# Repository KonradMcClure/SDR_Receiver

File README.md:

# Low-Cost Software Defined Radio Receiver
The goal of this project was to design a low-cost software-defined radio (SDR) receiver. This project was done for my Walla Walla University Electronics II course with my partner [Caleb Froelich](https://github.com/froeca).

## Design Objectives
Our professor, [Dr. Rob Frohne](https://github.com/frohro), gave us the following design objectives:
  1. Minimum discernible signal less than 1 uV
  2. Good image rejection
  3. Low noise figure
  4. Inexpensive to build ($25 component budget)
  
My partner, Caleb, and I set our own design objectives as well to help narrow down the design we settled on:
  1. **Simple Design**: We wanted our design to be easy to understand and construct. As such we avoided using transformers and used a Tayloe Mixer which has a relatively easy to understand design.
  2. **Ease of Construction**: Since this class took place during an online quarter due to COVID-19, we wanted to make sure construction wouldn't be too difficult without the usual tools we have in our lab. This decision shaped our board layout and part selection (picking through-hole parts as opposed to surface-mount when possible).
  3. **Ease and Quality of Amplification**: Most of the cost that goes into the board went into getting good, low-noise operational amplifiers. The instrumentation amps we chose use a single resistor to set the gain, making it easy to switch out and test different gain values.

## Overview
The Software Defined Radio (SDR) receiver connects to an antenna and covers the filtering, mixing, and amplification of the desired signal. It then connects a sound card within a computer and software handles the demodulation of the signal into playable audio. The mixing is handled using an Arduino Nano running code provided to us by our Professor, [Dr. Rob Frohne](https://github.com/frohro), which interfaces with [Quisk](https://james.ahlstrom.name/quisk/), an SDR that controls the receiver through the Arduino. Using Quisk, the radio can be tuned to a certain frequency by adjusting the speed of the local oscillator used in the mixing process. Our budget on this project to keep with the low-cost aspect was about $30 including fabrication of the PCB and the required components. 

# Theory

The basics of the SDR Receiver are shown above in the block diagram, with the blue components being defined by software. An antenna picks up the radio signal and passes it through a bandpass filter. This filter will attenuate any signals outside our desired range of 5 – 10 MHz. This is then passed through a Tayloe Mixer, also known as the Tayloe Quadrature Product Detector. The Tayloe Mixer is a simple and efficient mixer that uses a 1:4 demultiplexer and operational amplifiers to generate the I and Q quadrature signals for demodulation. After the signal has been split into four bandbase signals, they are amplified and combined into the I and Q quadrature signals. Those signals go through a final Low-Pass filter that will attenuate signals above 100KHz in frequency, effectively smoothing the output signal. This signal is then sent via 3.5mm audio cable to the soundcard which demodulates the signal. Quisk can then read the input from the sound card and play it. Quisk also interfaces to the Arduino Nano to set the speed of the local oscillator for tuning into the desired frequency.

# Rev 2 Design

Here is the full design schematic, which we'll break down piece by piece below. You can look at the full image [here](https://github.com/KonradMcClure/SDR_Receiver/blob/master/images/Schematics/Rev2_Schem.svg) or download the [KiCad](https://kicad-pcb.org/) project [here](https://github.com/KonradMcClure/SDR_Receiver/tree/master/SDRReciever) to take a closer look yourself.

This page is also acting as a report of the design we had for our class project. If the design is continued on in the future, I will likely move this description to the Wiki and update it with the new one.

## Bandpass Filter

The bandpass filter is a 3rd-Order, Series-First, Bessel filter that was generated using the RF Tools LC Filters Design Tool. It is designed to have input and output impedances of 50 Ω. The motivation to use a series-first configuration came from the capacitor C2 acting as a blockade for any DC signal coming in through the antenna. This would allow us better control over the DC voltage offset that is later required for our single-supply op-amps. 

## DC Voltage Offset

Since we didn't want to create a negative supply for our op-amps, we opted for using them with a single supply and giving our signal a DC offset that sits in the middle between the 4.3V supply and ground. This offset was done via a simple voltage divider of two 10k resistors from 4.3V to GND.

## Tayloe Mixer 

The Tayloe Mixer is a mixer design as seen in [this paper](http://www.norcalqrp.org/files/Tayloe_mixer_x3a.pdf) by Dan Tayloe. We chose it due to its relatively simple and elegant design. It utilizes a [two-channel SN74CBT multiplexer](http://www.ti.com/lit/ds/symlink/sn74cbt3253.pdf?ts=1591655665924) and a pair of [INA821ID single gain resistor instrumentation amplifiers](http://www.ti.com/lit/ds/symlink/ina821.pdf?HQS=TI-null-null-mousermode-df-pf-null-wwe&DCM=yes&ref_url=https%3A%2F%2Fwww.mouser.com%2F&distId=26). To be more specific, Tayloe describes this as a "switching integrator," rather than a mixer, since a mixer normally produces both a sum and difference frequency of the RF and LO signals, while this design only produces the difference frequency. Acknowledging this, I am going to refer to it as a mixer for simplicity.

### Multiplexer
The [SN74CBT multiplexer](http://www.ti.com/lit/ds/symlink/sn74cbt3253.pdf?ts=1591655665924) acts as a [product detector](https://en.wikipedia.org/wiki/Product_detector), converting the RF signal into four baseband signals. The switching speed of the MUX is set by the local oscillator, which is a divide by 4 circuit created from a 2-bit Johnson counter seen below. This speed is set to be the RF frequency + 10.7kHz. The sampling capacitors shown between the MUX and instrumentation amps will follow the voltage level of the signal while its line's switch is active, and then hold that value while the switch is closed. This will occur on four different lines, outputting four bandbase signals at phases of 0°, 90°, 180°, and 270°. 

### Instrumentation Amplifiers
The [INA821ID Instrumentation Amplifiers](http://www.ti.com/lit/ds/symlink/ina821.pdf?HQS=TI-null-null-mousermode-df-pf-null-wwe&DCM=yes&ref_url=https%3A%2F%2Fwww.mouser.com%2F&distId=26) act as differential summers of the 0° and 180° signals, and the 90° and 270° signals. This is because the information between the two signals within the two pairs are redundant to each other. Summing 0° and 180° will get us our In-Phase (I) signal and summing the 90° and 270° signals will get us our Quadrature (Q) signal.

## Lowpass Filter

Now that we have our I and Q signals, we'll send them through a Lowpass filter that will attenuate the high frequencies that may still remain in the signal, effectively smoothing it out. For this we used an [OP213FPZ op amp](https://www.analog.com/media/en/technical-documentation/data-sheets/OP113_213_413.pdf), which has 2-channel produces low noise. We used the [Texas Instruments Filter Design Tool](https://webench.ti.com/filter-design-tool/) to generate this as a two-pole filter with a 100kHz cutoff and no gain.

## Voltage Smoother and Analog Ground Reference

Professor Rob Frohne suggested that we all use a BJT to smooth the voltage coming from the computer, since all the rapid switching that happens in computers tends to create a lot of noise. He measured the output voltage to be about 4.3V based on the design on [his GitHub](https://github.com/frohro/IQ_SDR) , so we followed his example and designed ours the same way.

# Simulation
We simulated each of our main parts in LTspice to confirm our design. Some things, 

## Bandpass Filter Simulation

First we simulated the bandpass filter to check it's response. As seen here, and as mentioned later, our bandpass filter for Rev 2 got it's values messed up, which led to a similar, but incorrect response. We re-ran the RF Tools filter design and retested the response of our new filter in LTspice. As can be seen above, the response is much better. The filter on the bottom is calculated with 5% tolerances on all the components and then adjusted for the same toroids that we were provided by our professor. The differences between the bottom three are neglible, so only our current filter and the final adjusted one is plotted.

## Lowpass Simulation

We also tested out our lowpass filter. Luckily LTspice had the OP213's built-in, so we were confident in the results. We can see that the cutoff is at 100kHz as we expected. 

## Full Design Simulation

With the two filters out of the way, we can assemble the components inbetween. We have created a model for the mux using four voltage controlled switches, and four voltage pulses that control them in the same manner that the Johnson counter will. For instrumentation amps, we used LT1167s because they didn't take as long to simulate as long as ones we tried to import. The LT1167's had a much higher noise profile than the INA821's we selected, so we figured if we could get these to work, the INA821's would work great. below you can see the baseband signals and the I and Q outputs. They're exactly as we'd like to see them, about 90 degrees out of phase and at a frequency of about 10.8kHz.

# PCB Design

We sourced our board from [JLCPCB](https://jlcpcb.com/), who had an offer going of 5, 2-layer, 100x100mm boards for $2. With that size in mind, my partner and I both did our own board layouts and compared after to decide which to send in for printing. We wanted to be sure to match the impedance of the antenna all the way through to the instrumentation amps, so we used the PCB Calculator in KiCad to find the trace width we needed: 1.064mm. The input to the calculator can be seen here:

We got the rest of the information, such as the substrate parameters, from [JLCPCB's Capabilities page](https://jlcpcb.com/capabilities/Capabilities). The design shown above was mine, doing my best to keep traces relatively short and straight and parts close to the next. However...

# Construction and Testing
The PCB layout we decided to print was my partner's who had a layout with really nice divisions between sections, which we believed would be easier for testing. You can find that layout on [his GitHub page](https://github.com/froeca/Software-Defined-Radio). All of the components are exactly the same, only the layout is different.

Before receiving the parts from Dr. Frohne, JLCPCB, and Digikey, we put together a Construction and Testing plan which can be found in the documents folder of this repository. This plan wasn't followed exactly to the T during our assembly, but it was an important step for us thinking through the process and how to best assemble the sections so that we could test them in isolation before connecting them together.

# Testing
For info on the testing of the project, head over to the [Testing page on the Wiki](https://github.com/KonradMcClure/SDR_Receiver/wiki/Rev-2-Testing)!

# Quisk Setup
Loading the Arduino Nano with the OpenRadio software found [here](\Arduino\PSK), I opened the quisk_conf_openradio.py file and change the info in the SERIAL PORT SETTINGS sections to the COM# port that my Arduino is plugged into. This was found in Device Manager on Windows 10. In Device Manager, I also right clicked the COM port and went to Properties > Port Settings and changed the Bits per second to 57600 to match the value in the config file.

After opening Quisk, I went to Config > Radios and added a radio of the type SoftRock Fixed and named it MyRadioBoy (not necessary), setting it to open to that new radio. Under the new MyRadioBoy tab and Hardware subtab, I changed the Hardware File Path to point to the quisk_conf_openradio.py in the repository. Then in the Sound subtab, I made sure the I/Q Rx Sample Input was set to the sound card input that my 3.5mm cable was connected to from the board.

# Results!
Sending in a 8MHz test frequency, I could see that the image rejection was pretty good, but I went to the Config tab and clicked the "Adjust receive amplitude and phase" button. **I adjusted the levels for the best image rejection I could get, dropping the image down to about the same level as the spurious signals.**

Then, using a step attenuator Caleb and I designed before this radio, I input a 50uV 8MHz signal to the receiver and attenuated it by 40dB, which was just higher than the spurious signals. **From this I concluded our minimum discernable signal was about 0.5uV.**

After stringing a wire out to my roof as an antenna (about 50ft up or so) and soldering one end to an SMA connector, I connected it to the board. While not the clearest, it picks up signals pretty well! [You can see some signals that I was able to receive here!](https://github.com/KonradMcClure/SDR_Receiver/tree/master/video)

# Credits
My teammate [Caleb Froelich](https://github.com/froeca), who has [his own repository of this project](https://github.com/froeca/Software-Defined-Radio).

My professor [Dr. Rob Frohne](https://github.com/frohro), who provided us with an example of a similar [project of his own here](https://github.com/frohro/IQ_SDR)!

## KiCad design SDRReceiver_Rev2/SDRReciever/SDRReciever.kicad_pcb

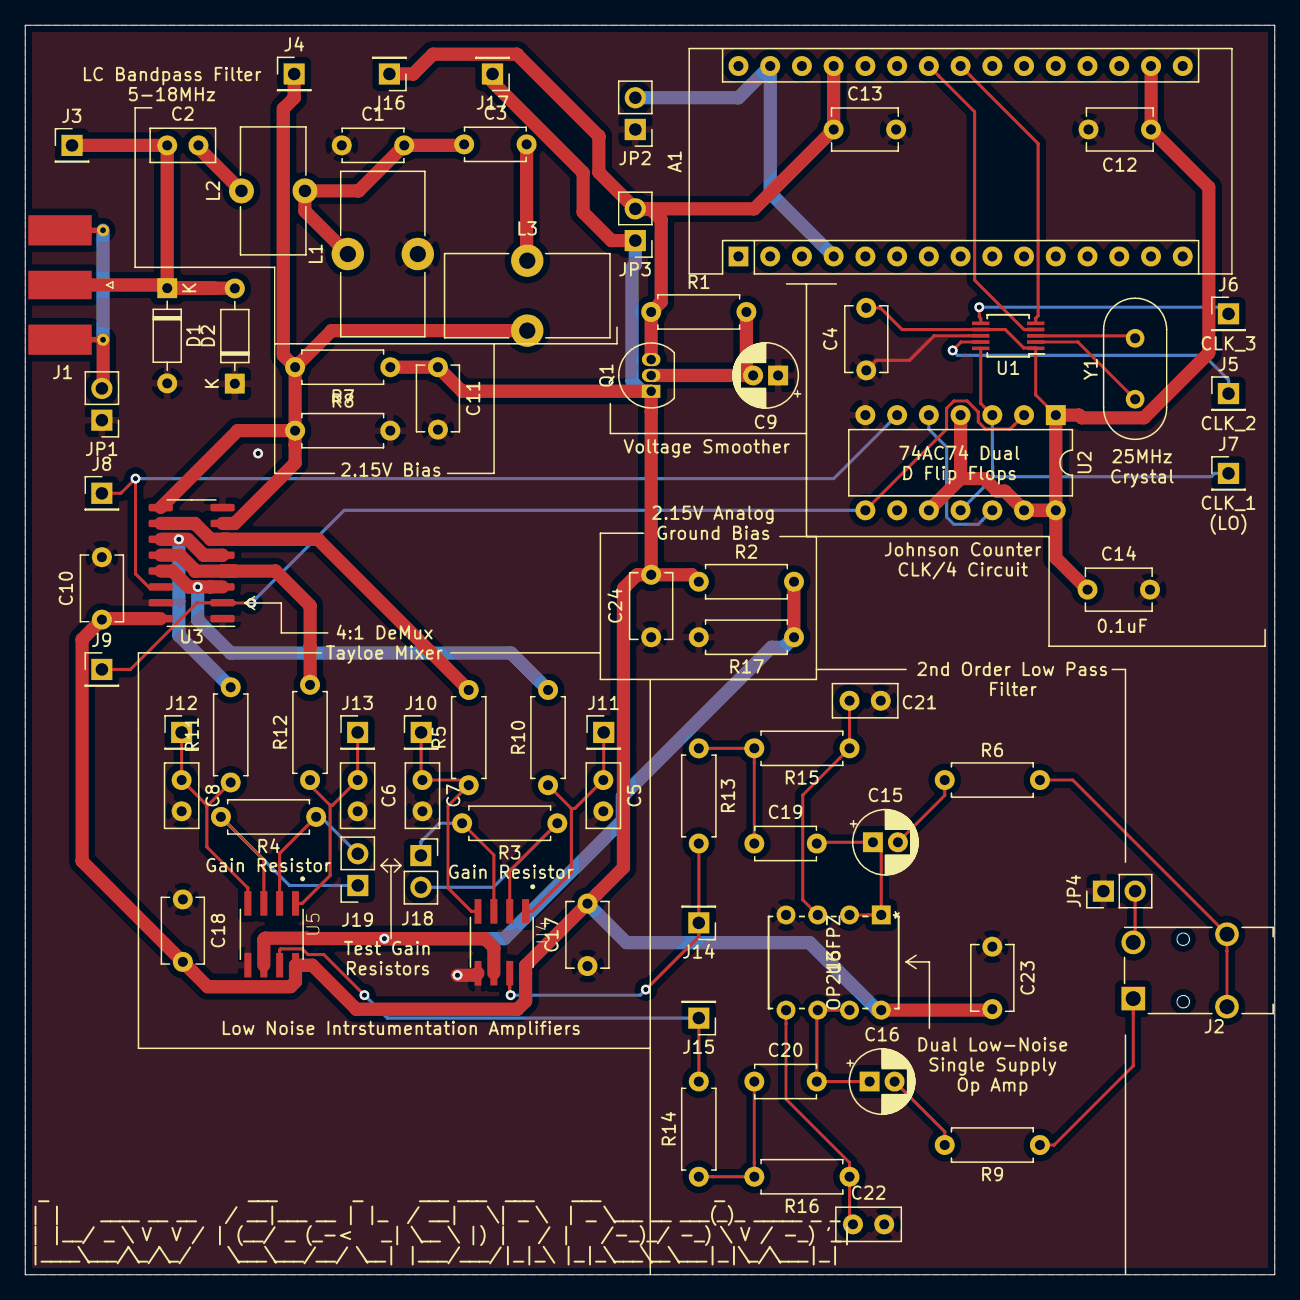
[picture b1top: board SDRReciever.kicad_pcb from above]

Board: 2 copper layers, 100.0 x 100.0 mm, 78 parts (0 on the bottom side), 48 nets.

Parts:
A1: Arduino_Nano_v3.x; Arduino_Nano
C1, C3: 220pF; C_Disc_D4.7mm_W2.5mm_P5.00mm
C2: 1nF; C_Disc_D5.0mm_W2.5mm_P2.50mm
C4, C10, C11, C12, C13, C14, C17, C18, C23, C24: 0.1u; C_Disc_D5.1mm_W3.2mm_P5.00mm
C5, C6, C7, C8, C21, C22: 100p; C_Disc_D5.0mm_W2.5mm_P2.50mm
C9, C15, C16: 10uF; CP_Radial_D5.0mm_P2.00mm
C19, C20: 220p; C_Disc_D4.7mm_W2.5mm_P5.00mm
D1, D2: 1N914; D_DO-35_SOD27_P7.62mm_Horizontal
J1: Conn_Coaxial; SMA_Molex_73251-1153_EdgeMount_Horizontal
J2: AudioJack3; Jack_3.5mm_Switronic_ST-005-G_horizontal
J3: FIL_I; PinHeader_1x01_P2.54mm_Vertical
J4: FIL_O; PinHeader_1x01_P2.54mm_Vertical
J5: CLK_2; PinHeader_1x01_P2.54mm_Vertical
J6: CLK_3; PinHeader_1x01_P2.54mm_Vertical
J7: CLK_1; PinHeader_1x01_P2.54mm_Vertical
J8: I_LO; PinHeader_1x01_P2.54mm_Vertical
J9: Q_LO; PinHeader_1x01_P2.54mm_Vertical
J10: I_0; PinHeader_1x01_P2.54mm_Vertical
J11: I_180; PinHeader_1x01_P2.54mm_Vertical
J12: Q_90; PinHeader_1x01_P2.54mm_Vertical
J13: Q_270; PinHeader_1x01_P2.54mm_Vertical
J14: I_OUT; PinHeader_1x01_P2.54mm_Vertical
J15: Q_OUT; PinHeader_1x01_P2.54mm_Vertical
J16: 5V; PinHeader_1x01_P2.54mm_Vertical
J17: 4.3V; PinHeader_1x01_P2.54mm_Vertical
J18, J19: Conn_01x02_Female; PinSocket_1x02_P2.54mm_Vertical
JP1, JP2, JP3, JP4: Jumper_NC_Small; PinHeader_1x02_P2.54mm_Vertical
L1, L3: 1.3uH; L_Toroid_Vertical_L13.0mm_W6.5mm_P5.60mm
L2: 200nH; L_Toroid_Vertical_L10.0mm_W5.0mm_P5.08mm
Q1: PN2222A; TO-92_Inline
R1: 1k; R_Axial_DIN0207_L6.3mm_D2.5mm_P7.62mm_Horizontal
R2, R7, R8, R17: 10k; R_Axial_DIN0207_L6.3mm_D2.5mm_P7.62mm_Horizontal
R3, R4: 33; R_Axial_DIN0207_L6.3mm_D2.5mm_P7.62mm_Horizontal
R5, R10, R11, R12: 50; R_Axial_DIN0207_L6.3mm_D2.5mm_P7.62mm_Horizontal
R6, R9: 100; R_Axial_DIN0207_L6.3mm_D2.5mm_P7.62mm_Horizontal
R13, R14: 8.2k; R_Axial_DIN0207_L6.3mm_D2.5mm_P7.62mm_Horizontal
R15, R16: 15k; R_Axial_DIN0207_L6.3mm_D2.5mm_P7.62mm_Horizontal
U1: Si5351A-B-GT; MSOP-10_3x3mm_P0.5mm
U2: 74AC74; DIP-14_W7.62mm
U3: SN74CBT3253; SOIC-16_3.9x9.9mm_P1.27mm
U4, U5: INA821ID; SOIC127P600X175-8N
U6: OP213FPZ
Y1: Crystal; Crystal_HC49-U_Vertical

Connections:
+3V3: A1.17, C4.2, C12.1, C14.1, U1.1, U1.7, U2.1, U2.4, U2.10, U2.13, U2.14
+4.3V: C10.1, C11.1, C17.2, C18.2, C23.2, C24.2, J17.1, JP3.1, Q1.1, R2.1, R7.1, U3.16, U4.8, U5.8, U6.8
+5V: A1.27, C13.1, J16.1, JP3.2, Q1.3, R1.1
/FIL_OUT: J4.1, L3.2, R7.2, R8.1, U3.7, U3.9
/I_LO: J8.1, U2.6, U3.14
/Q_LO: J9.1, U2.2, U2.8, U3.2
/SCL: A1.24, U1.4
/SDA: A1.23, U1.5
GND: C1.1, C4.1, C5.2, C6.2, C7.2, C8.2, C9.1, C10.2, C11.2, C12.2, C13.2, C14.2, C17.1, C18.1, C21.2, C22.2, C23.1, C24.1, D1.2, D2.1, JP1.1, JP2.1, JP4.1, L1.2, R8.2, R17.2, U1.8, U2.7, U3.1, U3.8, U3.15, U4.5, U5.5, U6.4
GNDA: R2.2, R17.1, U4.6, U5.6
unnamed: A1.4, A1.29, JP2.2
unnamed: C1.2, C3.1, L1.1, L2.2
unnamed: C2.1, D1.1, D2.2, J1.1, J3.1
unnamed: C2.2, L2.1
unnamed: C3.2, L3.1
unnamed: C5.1, J11.1, R10.1, U4.1
unnamed: C6.1, J13.1, R12.1, U5.1
unnamed: C7.1, J10.1, R5.1, U4.4
unnamed: C8.1, J12.1, R11.1, U5.4
unnamed: C9.2, Q1.2, R1.2
unnamed: C15.1, C19.2, U6.1, U6.2
unnamed: C15.2, R6.1
unnamed: C16.1, C20.2, U6.6, U6.7
unnamed: C16.2, R9.2
unnamed: C19.1, R13.1, R15.2
unnamed: C20.1, R14.1, R16.2
unnamed: C21.1, R15.1, U6.3
unnamed: C22.1, R16.1, U6.5
unnamed: J1.2, JP1.2
unnamed: J2.R, R9.1
unnamed: J2.S, JP4.2
unnamed: J2.T, R6.2
unnamed: J5.1, U1.9
unnamed: J6.1, U1.6
unnamed: J7.1, U1.10, U2.3, U2.11
unnamed: J14.1, R13.2, U4.7
unnamed: J15.1, R14.2, U5.7
unnamed: J18.1, R3.2, U4.3
unnamed: J18.2, R3.1, U4.2
unnamed: J19.1, R4.2, U5.3
unnamed: J19.2, R4.1, U5.2
unnamed: R5.2, U3.6, U3.10
unnamed: R10.2, U3.3, U3.13
unnamed: R11.2, U3.5, U3.11
unnamed: R12.2, U3.4, U3.12
unnamed: U1.2, Y1.1
unnamed: U1.3, Y1.2
unnamed: U2.5, U2.12

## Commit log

2020-06-05 new file: BOMs/CalebSDRReceiver_BOM.csv new file: BOMs/KonradSDRReceiver_BOM.csv new file: BOMs/SDRReceiverCartBOM_FroelichMcClure.xlsx new file: BOMs/SDRReceiverDigikeyBOM_FroelichMcClure.csv new fi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
2020-06-05 Added images
2020-06-05 Add Board Render to readme
2020-06-05 Added potentiometer, voltage buffer, clk gen pull up resistors, comments, and corrected gain resistors to 1k
2020-06-05 Added ltspice sims, revision document, image of the prototype, made some changes to the schematic (i believe just the title block)
2020-06-06 Changed PCB silkscreen title block, renamed some image files to be more specific to the revision they refer to, added SVGs for clearer documentation imagery
2020-06-06 Added notes to schematic and more images
2020-06-07 Fixed board render link
2020-06-07 Added issue4 testing images
2020-06-08 Added test images
2020-06-08 New board render
2020-06-08 Updated readme and layout
    Added quite a bit to the layout of the readme and fleshed it out
2020-06-08 Organized images and added schematic images
2020-06-08 Added images from schematic
2020-06-09 Added small versions of prototype images
2020-06-09 Moved Readme testing section to Wiki
2020-06-09 Even more images!'
2020-06-09 Added Rev2 full schem
2020-06-09 Added full schematic to readme
2020-06-09 Added Rev2 Project to it's own folder
2020-06-10 IT WORKS! Added videos!
2020-06-10 Spellcheck
2020-06-11 Added working images and video
2020-06-11 Updated sims and added sim images
2020-06-11 Updated withs simulation info
2020-06-11 Corrected with simulation image paths
2020-07-08 Fixed the Rev2 schematic from being pulled apart for screenshots

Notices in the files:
parts and their libraries:
Copyright 2016 Accelerated Designs. All rights reserved.
